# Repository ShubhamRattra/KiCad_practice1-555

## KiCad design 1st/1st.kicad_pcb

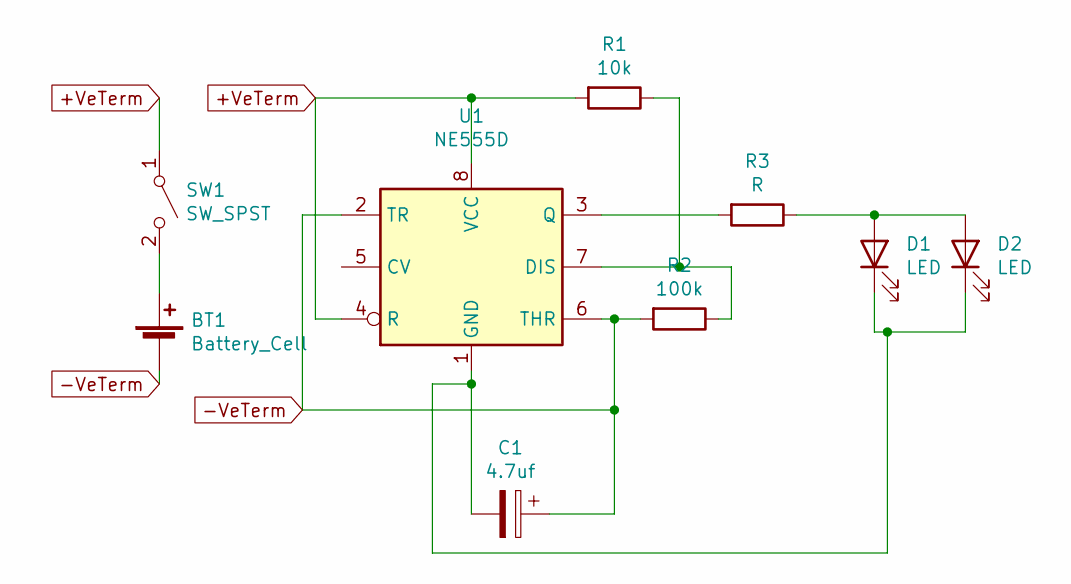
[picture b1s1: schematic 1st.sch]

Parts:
BT1: Battery_Cell; BatteryHolder_Keystone_1058_1x2032
C1: 4.7uf; CP_Radial_D6.3mm_P2.50mm
D1, D2: LED; LED_D3.0mm
R1: 10k; R_Axial_DIN0207_L6.3mm_D2.5mm_P7.62mm_Horizontal
R2: 100k; R_Axial_DIN0207_L6.3mm_D2.5mm_P7.62mm_Horizontal
R3: R; R_Axial_DIN0207_L6.3mm_D2.5mm_P7.62mm_Horizontal
SW1: SW_SPST; SW_PUSH_6mm_H7.3mm
U1: NE555D; DIP-8_W7.62mm

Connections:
+VeTerm: R1.2, SW1.1 (A), U1.4 (R), U1.8 (VCC)
-VeTerm: BT1.2 (-), C1.1, R2.2, U1.2 (TR), U1.6 (THR)
unnamed: BT1.1 (+), SW1.2 (B)
unnamed: C1.2, D1.1 (K), D2.1 (K), U1.1 (GND)
unnamed: D1.2 (A), D2.2 (A), R3.1
unnamed: R1.1, R2.1, U1.7 (DIS)
unnamed: R3.2, U1.3 (Q)

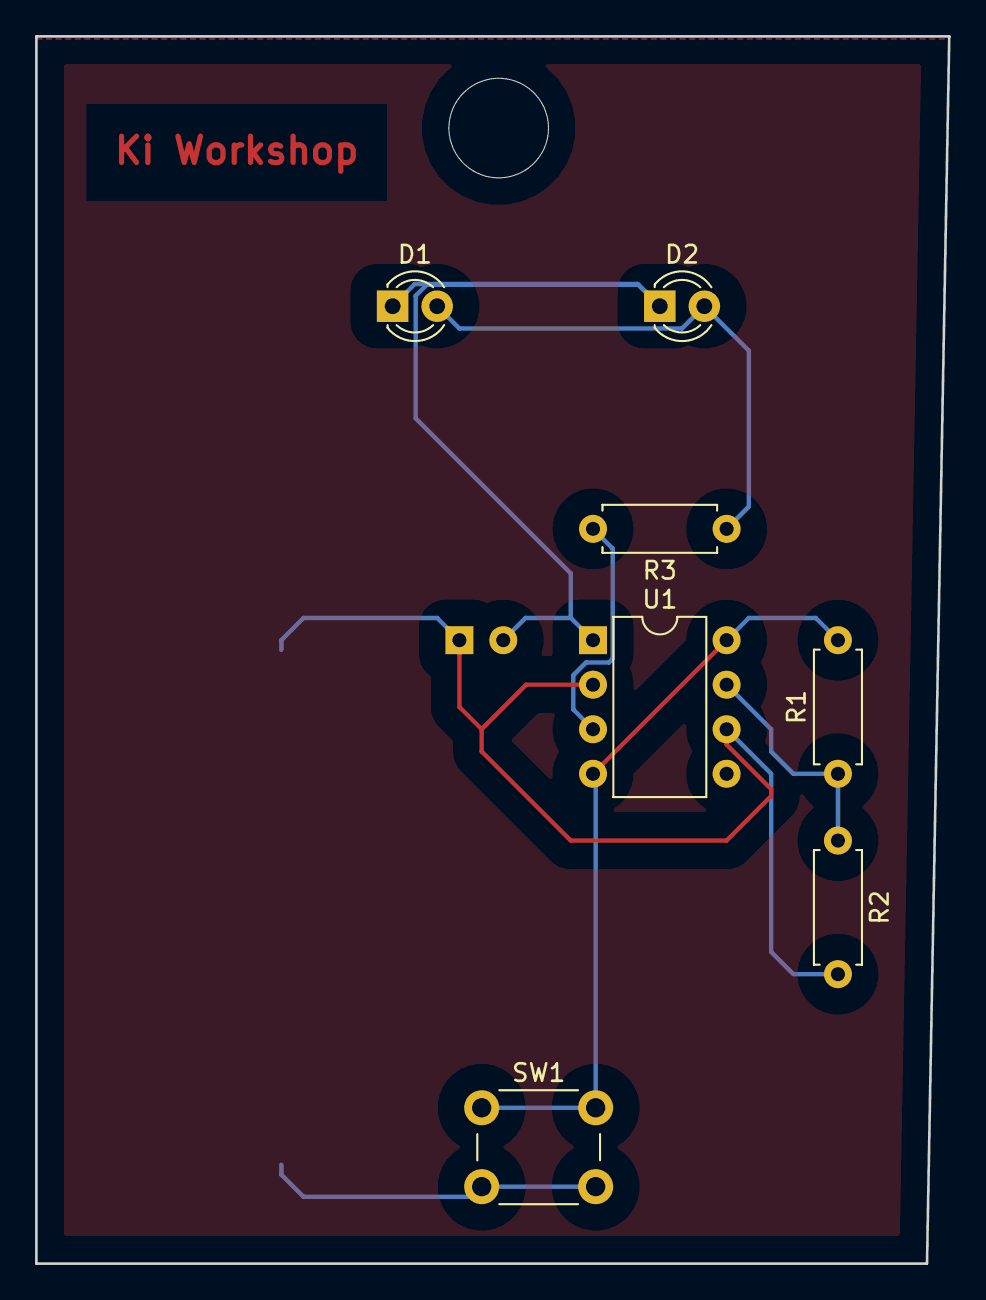
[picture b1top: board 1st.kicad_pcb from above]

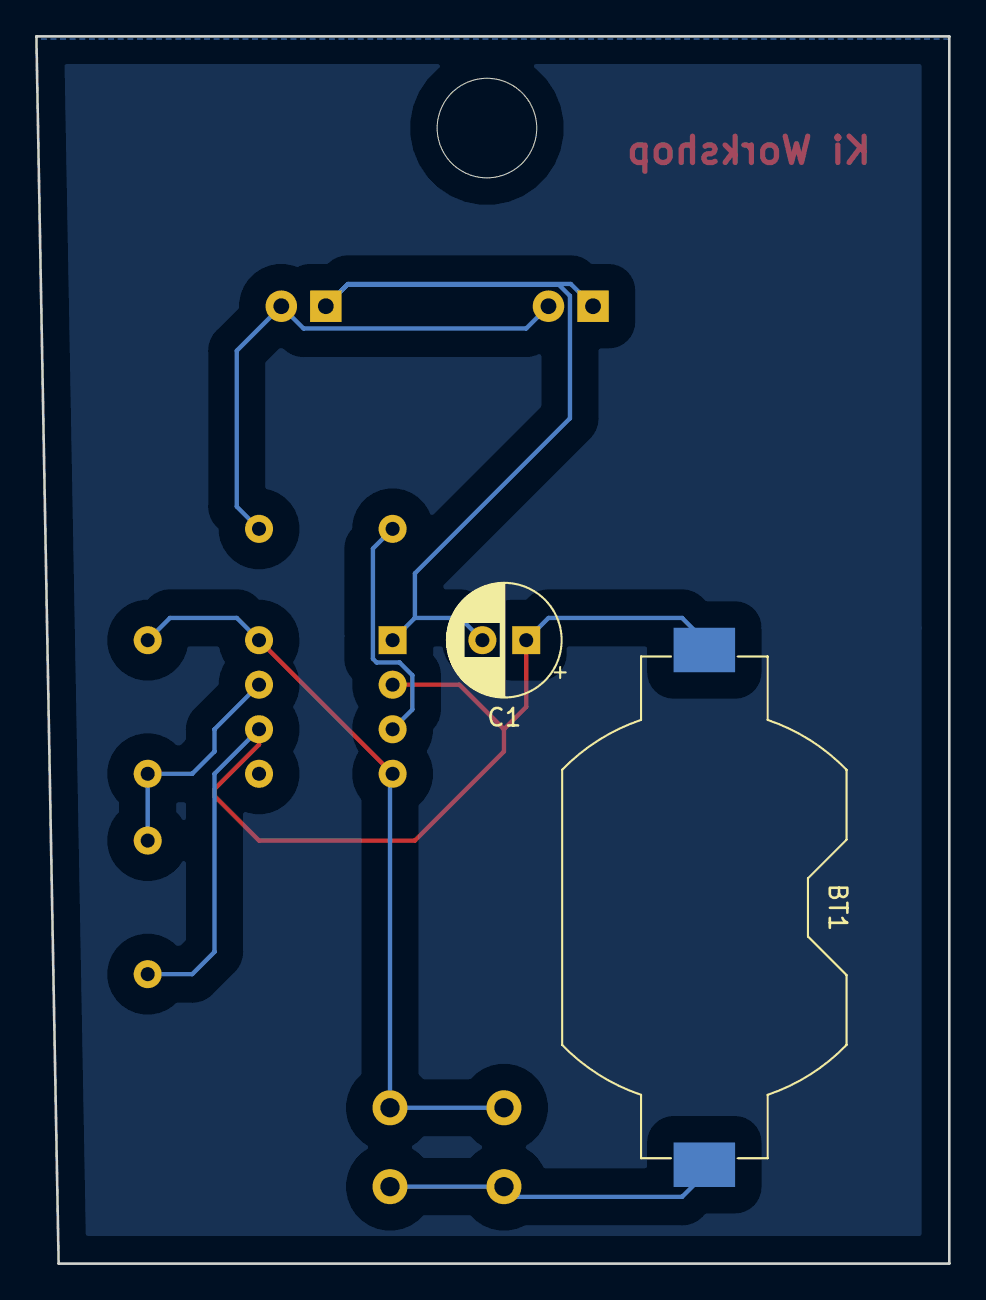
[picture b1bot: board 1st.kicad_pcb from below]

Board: 2 copper layers, 52.1 x 70.0 mm, 9 parts (2 on the bottom side), 7 nets.
